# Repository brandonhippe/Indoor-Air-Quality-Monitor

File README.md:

# 412AirQualityCapstone
2023 Portland State University ECE 412 Air Quality Capstone Project
<br>
<p>
We spend most of our lives indoors, but most of us lack the tools to assess the quality of the air
we breathe in those environments. Personal tools are available, albeit expensive, and must be
inconveniently carried with us along with all the other tools of our daily lives. Instead, we want to
make it easy to instrument buildings, continuously monitor the indoor environment, and report
data back to us. We can make it easy by making cheap, reliable devices that don't need
recharging for a long time. Three features of indoor air are expected to be monitored: 2.5 μm
particle count or PM2.5, carbon dioxide (CO2) concentration, and ventilation air speed.</p>
<br>
<p>
Regarding CO2, Statistically significant decrements occurred in cognitive performance
(decision making, problem resolution) starting at 1000 ppm . It is also a
good proxy for ventilation; high CO2 levels mean the room is poorly ventilated, which increases
the risk of passing airborne diseases such as COVID. After I finish Zoom meeting in a closed
room at home, the CO2 level is often over 1200!</p>
<br>
<p>
Regarding PM2.5, the WHO recommends an upper limit of 5 ug/m3 (microgram per cubic
meter) average annually and 15 ug/m3 average over a 24 hour period. As this project
document is being written, the outdoor air in Portland is over 30 ug/m3!</p>
<br>
<p>
An air speed sensor, or anemometer, can help us calculate how much air is flowing into or out of
a room and help understand why CO2 is high. The system should report an invalid value (e.g.,
not zero because zero airflow is a valid value) if the anemometer is not connected.</p>
<br>
<p>The system will be based on components past capstone teams have successfully incorporated
such as the TI MSP430 (including super low-power sleep modes). In this iteration, we will aim to
replace the closed-source proprietary SmartMesh IP wireless system with the OpenWSN
open-source wireless networking system.</p>
<br>
<h3>Project Goals</h3>
<br>
<p>Produce a fully wireless sensor data logger incorporating as many open-source components as
possible and able to be produced at a very low cost. A particular goal of this project is very low
power performance: sensors, communication system, and the microcontroller should be in as
low a power state as possible when not in use such that batteries need to be changed, at most,
annually. (The lifetime of a smoke detector would be even better!)</p>
<br>
<p>Data should be temporarily logged locally and wirelessly communicated to base station(s) as
appropriate. A stretch goal includes visualization dashboard to present the logged data
graphically for at-a-glance use. The device should be mechanically integrated into as small a
form-factor as is practical and contained in a robust housing appropriate for indoor
environments.</p>

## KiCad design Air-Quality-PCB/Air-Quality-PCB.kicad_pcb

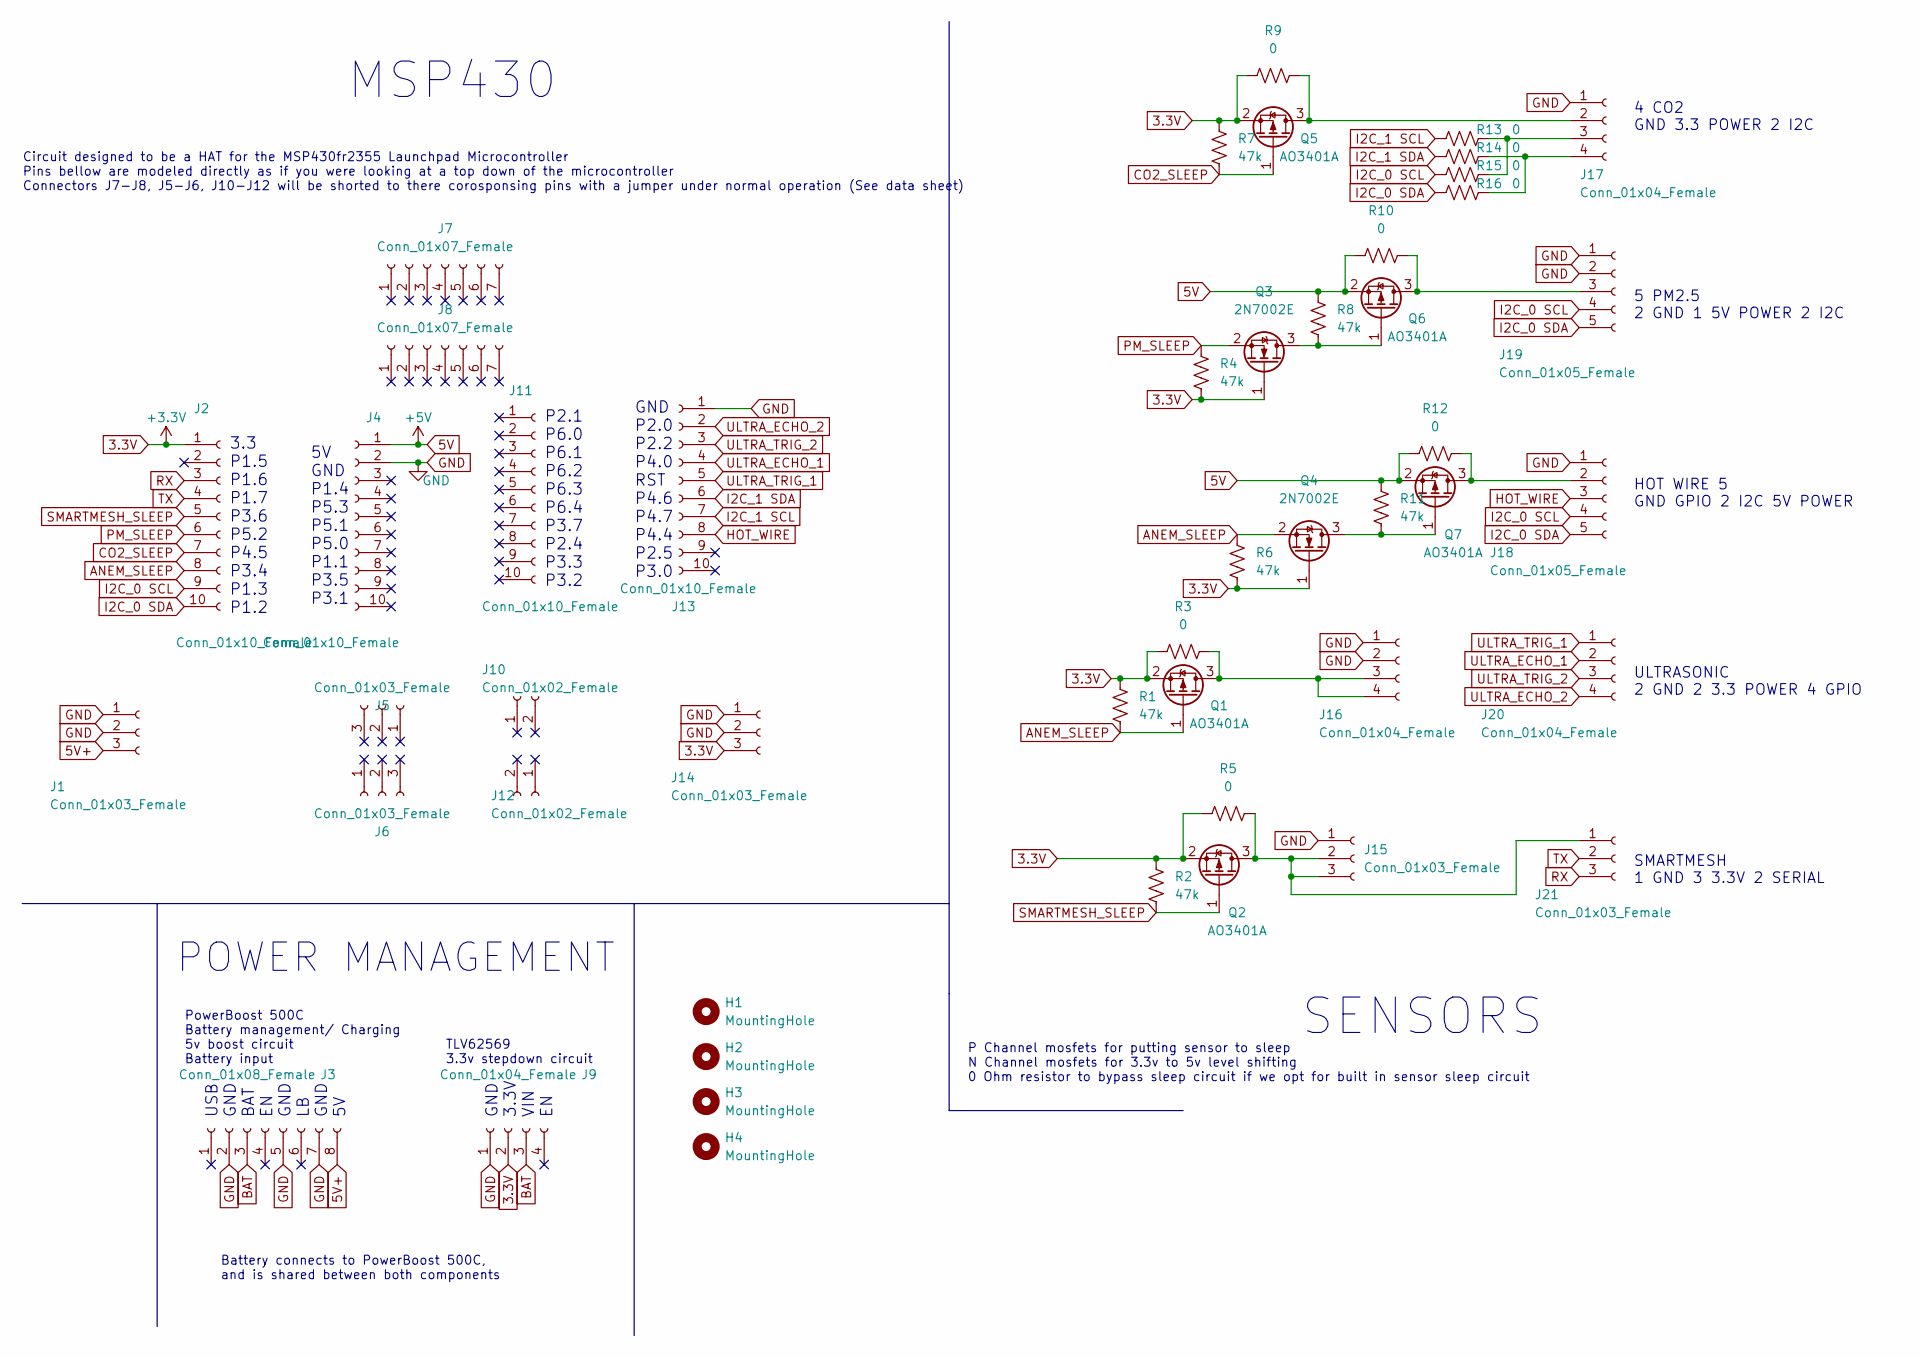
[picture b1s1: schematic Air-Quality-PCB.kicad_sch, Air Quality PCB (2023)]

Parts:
H1, H2, H3, H4: MountingHole; MountingHole_3.2mm_M3
J1: Conn_01x03_Female; PinSocket_1x03_P2.54mm_Vertical
J2, J13: Conn_01x10_Female; PinHeader_1x10_P2.54mm_Vertical
J3: Conn_01x08_Female; PinHeader_1x08_P2.54mm_Vertical
J4, J11: Conn_01x10_Female; PinSocket_1x10_P2.54mm_Vertical
J5, J6, J14, J15, J21: Conn_01x03_Female; PinHeader_1x03_P2.54mm_Vertical
J7, J8: Conn_01x07_Female; PinHeader_1x07_P2.54mm_Vertical
J9, J16, J17, J20: Conn_01x04_Female; PinHeader_1x04_P2.54mm_Vertical
J10, J12: Conn_01x02_Female; PinHeader_1x02_P2.54mm_Vertical
J18, J19: Conn_01x05_Female; PinSocket_1x05_P2.54mm_Vertical
Q1, Q2, Q5, Q6, Q7: AO3401A; SOT-23
Q3, Q4: 2N7002E; SOT-23
R1, R2, R4, R6, R7, R8, R11: 47k; R_1206_3216Metric
R3, R5, R9, R10, R12, R13, R14, R15, R16: 0; R_1206_3216Metric

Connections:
3.3V: J2.1, J9.2, J14.3, Q1.2 (S), Q2.2 (S), Q3.1 (G), Q4.1 (G), Q5.2 (S), R1.1, R2.1, R3.1, R4.2, R5.1, R6.2, R7.1, R9.1
5V: J4.1, Q6.2 (S), Q7.2 (S), R8.1, R10.1, R11.1, R12.1
5V+: J1.3, J3.8
ANEM_SLEEP: J2.8, Q1.1 (G), Q4.2 (S), R1.2, R6.1
BAT: J3.3, J9.3
CO2_SLEEP: J2.7, Q5.1 (G), R7.2
GND: J1.1, J1.2, J3.2, J3.5, J3.7, J4.2, J9.1, J13.1, J14.1, J14.2, J15.1, J16.1, J16.2, J17.1, J18.1, J19.1, J19.2
HOT_WIRE: J13.8, J18.3
I2C_0 SCL: J2.9, J18.4, J19.4, R15.1
I2C_0 SDA: J2.10, J18.5, J19.5, R16.1
I2C_1 SCL: J13.7, R13.1
I2C_1 SDA: J13.6, R14.1
unnamed: J15.2, J15.3, J21.1, Q2.3 (D), R5.2
unnamed: J16.3, J16.4, Q1.3 (D), R3.2
unnamed: J17.2, Q5.3 (D), R9.2
unnamed: J17.3, R13.2, R15.2
unnamed: J17.4, R14.2, R16.2
unnamed: J18.2, Q7.3 (D), R12.2
unnamed: J19.3, Q6.3 (D), R10.2
unnamed: Q3.3 (D), Q6.1 (G), R8.2
unnamed: Q4.3 (D), Q7.1 (G), R11.2
PM_SLEEP: J2.6, Q3.2 (S), R4.1
RX: J2.3, J21.3
SMARTMESH_SLEEP: J2.5, Q2.1 (G), R2.2
TX: J2.4, J21.2
ULTRA_ECHO_1: J13.4, J20.2
ULTRA_ECHO_2: J13.2, J20.4
ULTRA_TRIG_1: J13.5, J20.1
ULTRA_TRIG_2: J13.3, J20.3

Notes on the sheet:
Battery connects to PowerBoost 500C, and is shared between both components
GND 3.3V VIN EN
P2.1 P6.0 P6.1 P6.2 P6.3 P6.4 P3.7 P2.4 P3.3 P3.2
SENSORS
3.3 P1.5 P1.6 P1.7 P3.6 P5.2 P4.5 P3.4 P1.3 P1.2
GND P2.0 P2.2 P4.0 RST P4.6 P4.7 P4.4 P2.5 P3.0
5V GND P1.4 P5.3 P5.1 P5.0 P1.1 P3.5 P3.1
4 CO2 GND 3.3 POWER 2 I2C 5 PM2.5 2 GND 1 5V POWER 2 I2C HOT WIRE 5 GND GPIO 2 I2C 5V POWER ULTRASONIC 2 GND 2 3.3 POWER 4 GPIO SMARTMESH 1 GND 3 3.3V 2 SERIAL
TLV62569 3.3v stepdown circuit
USB GND BAT EN GND LB GND 5V
Circuit designed to be a HAT for the MSP430fr2355 Launchpad Microcontroller Pins bellow are modeled directly as if you were looking at a top down of the microcontroller Connectors J7-J8, J5-J6, J10-J12 will be shorted to there corosponsing pins with a jumper under normal operation (See data sheet)
MSP430
P Channel mosfets for putting sensor to sleep N Channel mosfets for 3.3v to 5v level shifting 0 Ohm resistor to bypass sleep circuit if we opt for built in sensor sleep circuit
PowerBoost 500C Battery management/ Charging 5v boost circuit Battery input
POWER MANAGEMENT

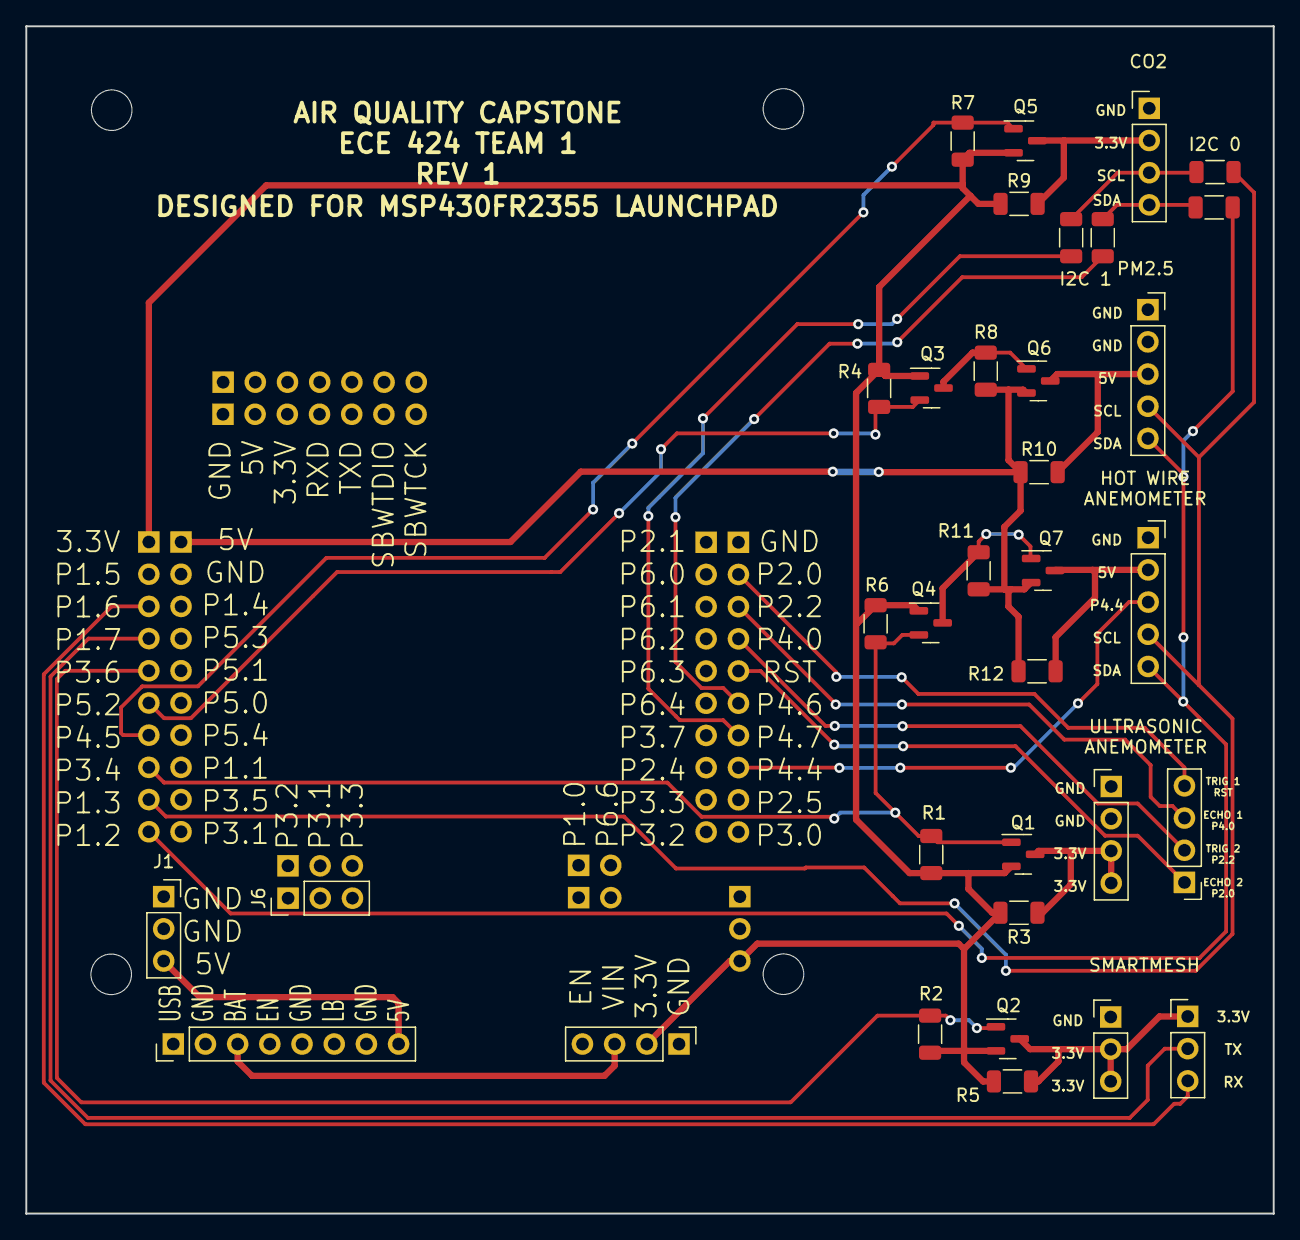
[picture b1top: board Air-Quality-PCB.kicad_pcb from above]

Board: 2 copper layers, 98.4 x 93.7 mm, 48 parts (0 on the bottom side), 29 nets.

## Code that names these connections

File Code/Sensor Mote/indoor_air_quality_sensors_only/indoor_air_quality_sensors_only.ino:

#include <sgp30.h>
#include <sps30.h>


#define powerTest false


#define SCL 9
#define SDA 10
#define LB 27


#define ANEM_SLEEP_PIN 5   // Set Anemometer sleep pin to 5 to enable, 0 to disable
#define PM_SLEEP_PIN 6    // Set PM sleep pin to 6 to enable, 0 to disable
#define CO2_SLEEP_PIN 7   // Set CO2 sleep pin to 7 to enable, 0 to disable


#define BATTERY_LIFE 2    // Set to 0 for 1 year, 1 for 6 months, or 2 for 3 months


#define SPS_FP true		// Set to true for PM sensor floating point values, false for 16-bit unsigned integers

/*// Uncomment this section for Climate Guard Anemometer
  #include <cgAnem.h>
  CG_Anem anem;
  #define ANEM_OFFSET 0
  //*/


// Uncomment this section for Ultrasonic Anemometer
#include <UltrasonicAnem.h>
UltrasonicAnem anem;
#define ANEM_OFFSET 1
//*/


#define debug true


uint64_t time_ms, nextTime;


SGP30 co2;
SPS30 pm;


uint8_t nextDevice;
#define CO2 0
#define PM 1
#define ANEM 2
#define TEST 3


bool anem_present;


const uint64_t pm_periods[3][3] =   {{4320000, 15600000, 6300000},
                                     {2040000,  6600000, 2880000},
                                     { 960000,  2820000, 1320000}};
                                  
const uint64_t co2_periods[3][3] =  {{2220000, 13200000, 3060000},
                                     {1080000,  5400000, 1500000},
                                     { 510000,  2400000,  720000}};
                                  
const uint64_t anem_periods[3][3] = {{0xFFFFFFFFFFFFFFFF, 5160000, 40000},
                                     {0xFFFFFFFFFFFFFFFF, 2160000, 20000},
                                     {0xFFFFFFFFFFFFFFFF,  960000, 10000}};


bool alertSent = false;


void nextDev() {
  nextTime = co2.time_ms;
  nextDevice = CO2;

  if (pm.time_ms < nextTime) {
    nextTime = pm.time_ms;
    nextDevice = PM;
  }

  if (anem_present && anem.time_ms < nextTime) {
    nextTime = anem.time_ms;
    nextDevice = ANEM;
  }

  if (nextTime == 0xFFFFFFFFFFFFFFFF) {
    Serial.println("TEST DEV");
    nextTime = millis() + 10000;
    nextDevice = TEST;
  }
}


void setup() {
  Serial.begin(9600);
  Serial.println("Starting");
  
  for (int i = 1; i <= 40; i++) {
    digitalWrite(i, LOW);
    pinMode(i, OUTPUT);
  }

  pinMode(1, INPUT);
  pinMode(21, INPUT);

  pinMode(SCL, INPUT_PULLUP);
  pinMode(SDA, INPUT_PULLUP);
  pinMode(LB, INPUT_PULLUP);

  int max_clock = 400000;
  if (co2.max_clock < max_clock) {
    max_clock = co2.max_clock;
  }

  if (pm.max_clock < max_clock) {
    max_clock = pm.max_clock;
  }

  if (anem.max_clock < max_clock) {
    max_clock = anem.max_clock;
  }

  Wire.setModule(0);
  Wire.begin();
  Wire.setClock(max_clock);

  bool sensed = false;

  // Initialize PM Sensor
  sensed = pm.begin(MCPM2p5, SPS_FP, debug, PM_SLEEP_PIN);
  if (!sensed) {
    if (debug) Serial.println("ERROR: PM sensor not connected!");
    while (!powerTest);
  }

  // Initialize CO2 Sensor
  sensed = co2.begin(debug, CO2_SLEEP_PIN);
  if (!sensed) {
    if (debug) Serial.println("ERROR: CO2 sensor not connected!");
    while (!powerTest);
  }

  // Initialize Anemometer, if present
  anem_present = anem.begin(ANEM_SLEEP_PIN, debug);
  if (anem_present) {
    if (debug) Serial.println("Anemometer connected!");
  } else {
    if (debug) Serial.println("Anemometer not connected!");
    anem.time_ms = 0xFFFFFFFFFFFFFFFF;
  }

  // Set Measurement Periods
  if (!powerTest) {
    if (anem_present) {
      pm.period_ms = pm_periods[BATTERY_LIFE][1 + ANEM_OFFSET];
      co2.period_ms = co2_periods[BATTERY_LIFE][1 + ANEM_OFFSET];
      anem.period_ms = anem_periods[BATTERY_LIFE][1 + ANEM_OFFSET];
      Serial.println((uint32_t)pm.period_ms);
      Serial.println((uint32_t)co2.period_ms);
      Serial.println((uint32_t)anem.period_ms);
    } else {
      pm.period_ms = pm_periods[BATTERY_LIFE][0];
      co2.period_ms = co2_periods[BATTERY_LIFE][0];
      anem.period_ms = anem_periods[BATTERY_LIFE][0];
      Serial.println((uint32_t)pm.period_ms);
      Serial.println((uint32_t)co2.period_ms);
    }
  }

  if (debug) Serial.println("Sleeping to first device function");
  nextDev();
  time_ms = nextTime;
  if (time_ms > millis()) {
    sleep(time_ms - millis());
  }
}

void loop() {
  if (digitalRead(LB) && alertSent) {
    alertSent = false;
    if (debug) Serial.println("Battery Charged");
  }
  
  if (!digitalRead(LB) && !alertSent) {
    alertSent = true;
    if (debug) Serial.println("ALERT: LOW BATTERY");
  } else {
    // Execute next function
    Serial.println("Started loop execution");
    uint32_t startTime = millis();
  
    if (debug) Serial.println("Performing device function");
    switch (nextDevice) {
      case CO2:
        if (debug) Serial.println("eCO2");
  
        if (anem_present && ANEM_SLEEP_PIN != 0 && ANEM_OFFSET == 0) anem.cg_wakeup();
        co2.startNextFunc(time_ms + startTime - millis());
        if (co2.measurement_ready && anem_present && ANEM_SLEEP_PIN != 0 && ANEM_OFFSET == 0) anem.cg_sleep();
  
        break;
      case PM:
        if (debug) Serial.println("PM");
  
        if (anem_present && ANEM_SLEEP_PIN != 0 && ANEM_OFFSET == 0) anem.cg_wakeup();
        if (CO2_SLEEP_PIN != 0) co2.sgp30_wakeup_transistor();
        pm.startNextFunc(time_ms + startTime - millis());
        if (pm.measurement_ready && anem_present && ANEM_SLEEP_PIN != 0 && ANEM_OFFSET == 0) anem.cg_sleep();
        if (pm.measurement_ready && CO2_SLEEP_PIN != 0) co2.sgp30_sleep_transistor();
        break;
      case ANEM:
        if (debug) Serial.println("Anemometer");
  
        if (CO2_SLEEP_PIN != 0) co2.sgp30_wakeup_transistor();
        anem.startNextFunc(time_ms + startTime - millis());
        if (anem.measurement_ready && CO2_SLEEP_PIN != 0) co2.sgp30_sleep_transistor();
  
        break;
    }
  }

  // Print out measurements
  if (debug) {
    Serial.println("Device Function Finished");
    switch (nextDevice) {
      case CO2:
        if (co2.measurement_ready) {
          Serial.print("eCO2: ");
          Serial.print(co2.co2);
          Serial.println(" ppm");
        }
        break;
      case PM:
        if (pm.measurement_ready) {
          switch (pm.measurementIx) {
            case MCPM2p5:
              Serial.print("PM2.5 ");
              if (pm.fp) {
                Serial.print(pm.pm2p5_float);
              } else {
                Serial.print(pm.pm2p5_int);
              }
              Serial.println(" ug/m3");
              break;
            case NCPM2p5:
              Serial.print("PM2.5 ");
              if (pm.fp) {
                Serial.print(pm.pm2p5_float);
              } else {
                Serial.print(pm.pm2p5_int);
              }
              Serial.println(" per cm3");
              break;
          }
        }
        break;
      case ANEM:
        if (anem.measurement_ready) {
          Serial.print("Airflow: ");
          Serial.print(anem.airflowRate);
          Serial.println(" m/s");
        }
        break;
    }
  }

  // Execution finished, find next function
  if (debug) Serial.println("Finding next function");
  nextDev();
  // Calculate time until next function
  // Check if millis() has overflowed
  uint32_t currTime_32 = millis();
  uint64_t currTime_ms = (time_ms & 0xFFFFFFFF00000000) + currTime_32;
  if (currTime_ms < time_ms) {
    if (debug) Serial.println("millis() overflowed!");
    currTime_ms += 0x0000000100000000;
  }

  // If next time hasn't passed, sleep until then
  if (debug) Serial.println("Sleeping\n");
  if (nextTime > currTime_ms + (millis() - currTime_32)) {
    uint32_t sleepTime = nextTime - (currTime_ms + (millis() - currTime_32));
    if (debug) Serial.println(sleepTime);
    uint64_t i;
    for (i = 0xFFFFFFFFFFFFFFFF; (i + 65536) < sleepTime && (digitalRead(LB) || alertSent); i += 65536) {
      if (debug) Serial.println((uint32_t)i);
      sleep(65536);
    }

    if (i + 65536 < sleepTime) {
      time_ms = nextTime - sleepTime + i + 1;
    } else {
      sleep(sleepTime % 65536);
      time_ms = nextTime;
    }
  } else {
    time_ms = currTime_ms + (millis() - currTime_32);
  }

  Serial.println();
}

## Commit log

2023-01-08 Added gitignore
2023-01-08 Added Project Description Doc
2023-01-08 Configuration power consumption calculator added
2023-01-09 Updated gitignore
2023-01-09 Added battery capacity calculations
2023-01-11 Added Microcontroller Duty Cycle Calculation
2023-01-13 Added 18650 Cell Calculation
2023-01-13 Added input and output files
2023-01-13 Create LICENSE
2023-01-13 Updated with SPS30
2023-01-13 Added per-component sleep mode percentage calculation
2023-01-16 Added Excel file of Gantt Chart
    Does need to be updated after meeting with team
2023-01-19 Ultrasonic Anemometer
2023-01-19 Graphing added
2023-01-22 Added Period Calculation
2023-01-22 Ultrasonic Sensor Testing
2023-01-22 Modified Group Sorting
2023-01-23 Added detailed component analysis
2023-01-25 Create Images
    created new file to house all photos for project and wiki
2023-01-25 Create placeholder
    Created images folder to house images of project
2023-01-25 Add files via upload
    uploaded power consumption test for all possible sensors
2023-01-31 added L1 diagrams
2023-02-01 added spring and winter timelines
2023-02-10 Updated Power Consumption Calculations
2023-02-10 Added Ultrasonic Anemometer Test Code
2023-02-10 Added Proposal Draft
2023-02-14 Modified Graph and Text Output Formatting
2023-03-27 I2C Test
2023-03-27 Modified ultrasonic pulse generation code
2023-03-27 SGP30/SPS30 Datasheets
2023-03-27 Created SGP30 and SPS30 libraries with test code
2023-04-04 Created main scheduling code and updated SPS30/SGP30 libraries
2023-04-06 Refactor CO2 and PM Sensor libraries to use non-blocking code compatible with sleep Added example code for CO2 and PM sensors
2023-04-06 Updated main program with modified libraries
2023-04-12 Moved sensor test code into library example folders
2023-04-12 SPS30 UART Test
2023-04-12 Anemometer Datasheet
2023-04-13 Added sensor spoofing
2023-04-13 Fixed I2C initialization
2023-04-15 Fixed CRC checks
2023-04-15 Added New Wire library, with larger rx/tx buffer size
2023-04-15 Update gitignore
2023-04-15 Fixed SPS30 library
2023-04-15 Initial SGP30 library fix
2023-04-15 Added Anemometer library
2023-04-15 Update main code with sensor fixes and begin anemometer implementation
2023-04-17 Full hardware prototype (minus SmartMesh and Anemometer testing) finished
2023-04-17 Breadboard prototype image
2023-04-19 Fixed first measurement scheduling
2023-04-19 Added Ultrasonic Anemometer Library
2023-04-19 Relocated Power Testing Data/Code
2023-04-24 Fixed SGP30 not going into sleep
2023-04-28 Added MSP430 Pinout Diagram
2023-04-28 Started power consumption testing
2023-04-28 Modified gitignore
2023-04-28 Period changes for power consumption testing
2023-05-01 Ki-Cad first round
2023-05-01 Added Smartmesh Libraries
2023-05-06 Created V2 Code with Smartmesh Implementation
2023-05-08 Created Sensor Mote code folder
2023-05-08 Added Host Node Python scripts and started modifications
2023-05-08 Simplified node code to prepare for integration with modified Host Node code
2023-05-08 Added initial enclosure CAD files
2023-05-08 Added floating point capability to host code
2023-05-08 Store received data in log as single integer, rather than (sensor, value) pair
2023-05-08 Added example log file
2023-05-08 Fixed example log format
2023-05-08 Fixed receiver printing out example log file as a known mote
2023-05-08 Hotwire Anemometer fixes
2023-05-09 Switched to Hex representation in log file
2023-05-09 CG Anem Fixes
2023-05-09 Added example log files
2023-05-12 Laser Cutting file added
2023-05-16 Convert enclosure files to STL and add laser cutting DXF file
2023-05-16 Initial power testing data added and periods modified
2023-05-16 Updated measurement calculations
2023-05-16 V2 Laser cutting
2023-05-16 Added transistor shutoff code
2023-05-18 Started new graphing script
2023-05-18 Library fixes for PCB
2023-05-18 Examples plotted
2023-05-18 Added files from previous team
    added last years final report
2023-05-20 Add files via upload
    added website work
2023-05-25 uploaded website
    V0.2
2023-06-03 Power testing completed
2023-06-03 Graphing script start
2023-06-03 Example log file fix
2023-06-03 Sensor fixes, add low battery alert, add battery life configuration
2023-06-03 Remove graphing test
2023-06-03 Low Battery alert start
2023-06-03 SGP30 Calibration stopped
2023-06-03 Removed calibration
2023-06-05 Changed CO2 to average over 15 seconds
2023-06-05 Fixed lines for same sensor node on different plots to be the same color
2023-06-05 Added renaming using User ID Line
2023-06-05 Added Low Battery Alert
2023-06-07 Attempt to get Ultrasonic Anemometer functioning
2023-06-07 Added units to plots
2023-06-08 Changed plot style
2023-06-08 Plot Formatting
2023-06-09 Added timestamp to low battery alert
2023-06-09 Remove previous graphing script
2023-06-09 Recalculate Hotwire Anemometer periods and change hotwire anemometer to take data when turned on to run another sensor
2023-06-09 Anemometer Changes
2023-06-09 CO2 Troubleshooting
2023-06-09 Added averaging/max value
2023-06-09 Added average/max select
2023-06-19 # This is a combination of 5 commits. # This is the 1st commit message:
    Added average/max select
    # This is the commit message #2:
    Upload Google Drive Files
    # This is the commit message #3:
    Added Final Report and fixed anemometer only mode
    # This is the commit message #4:
2023-07-21 Fixed requestService call causing mote disconnection
2023-08-08 Fixed motes failing power-on
2023-08-18 Removed example button, plotted example data by default, and fixed background color
2023-08-22 Set fixed legend location
2023-10-23 PurpleAir Data
2023-10-23 Graphing Script Changes
2023-10-23 SGP30/CG Anem Fix Attempts
2023-10-23 SCD40/41 Implementation with V3 Code
2023-10-23 SCD41 Power Testing
2023-11-09 Anemometer Example Fix
2024-03-06 Update logfile reading to better handle large files
2024-09-11 Add rerun.io visualization support
2025-01-16 Add requirements.txt
2025-01-17 Update matplotlib version
